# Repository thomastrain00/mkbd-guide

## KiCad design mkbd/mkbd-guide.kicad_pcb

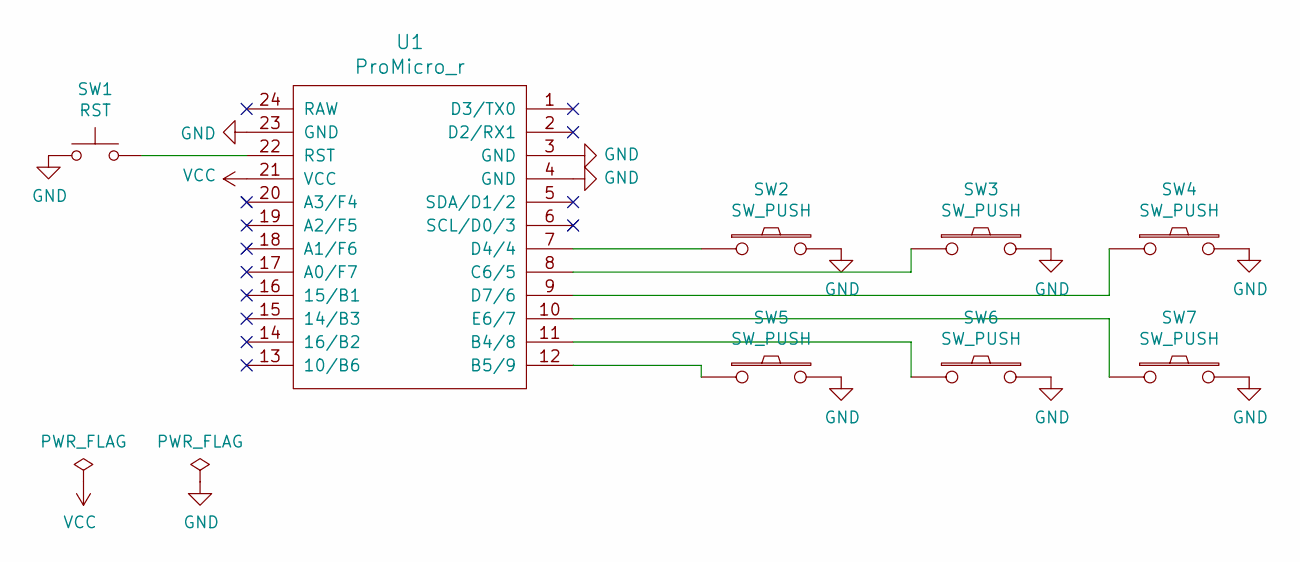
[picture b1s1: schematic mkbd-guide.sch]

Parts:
SW1: RST; ResetSW
SW2, SW3, SW4, SW5, SW6, SW7: SW_PUSH; CherryMX_1u
U1: ProMicro_r; ProMicro_v3

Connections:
GND: SW1.1, SW2.2, SW3.2, SW4.2, SW5.2, SW6.2, SW7.2, U1.3 (GND), U1.4 (GND), U1.23 (GND)
unnamed: SW1.2, U1.22 (RST)
unnamed: SW2.1, U1.7 (D4/4)
unnamed: SW3.1, U1.8 (C6/5)
unnamed: SW4.1, U1.9 (D7/6)
unnamed: SW5.1, U1.12 (B5/9)
unnamed: SW6.1, U1.11 (B4/8)
unnamed: SW7.1, U1.10 (E6/7)
VCC: U1.21 (VCC)

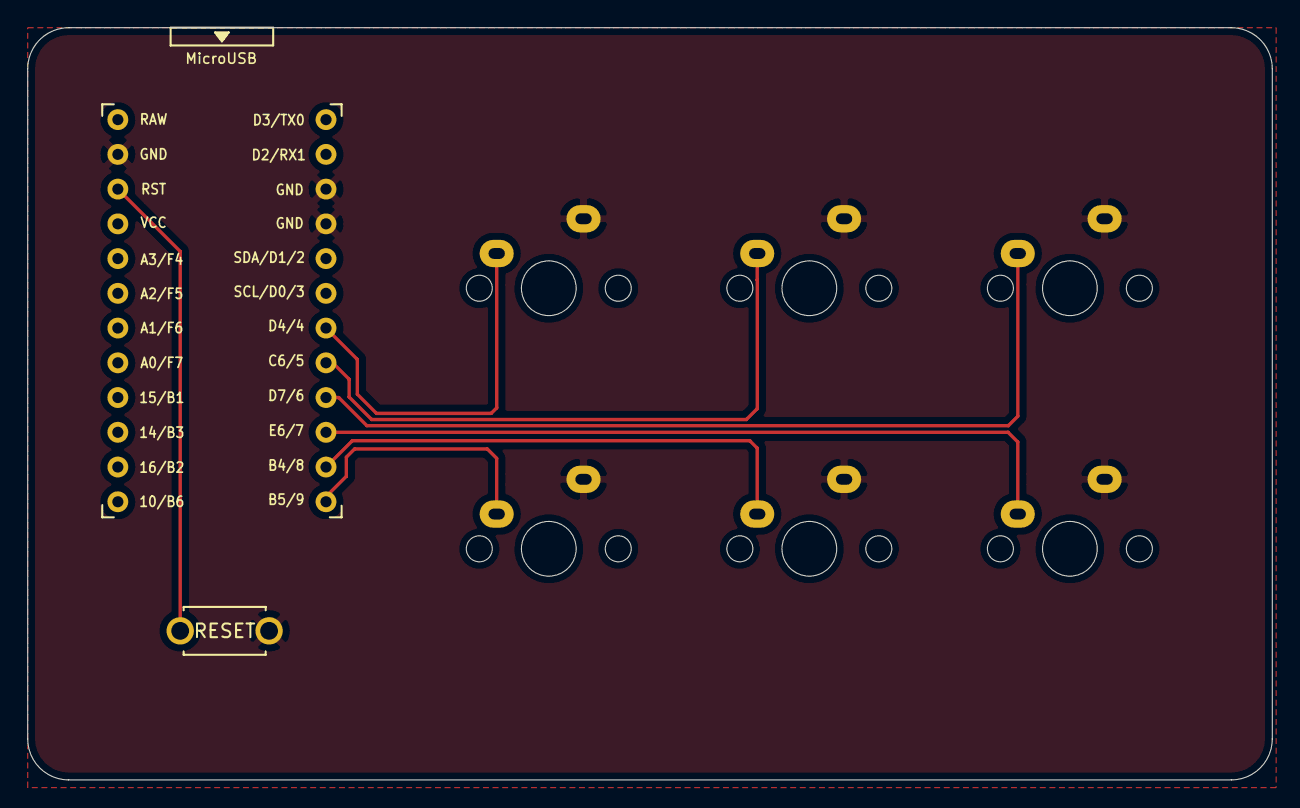
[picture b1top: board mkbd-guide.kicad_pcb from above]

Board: 2 copper layers, 91.0 x 55.0 mm, 8 parts (0 on the bottom side), 8 nets.

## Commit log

2021-05-15 Initialize project files
2021-05-16 Finished PCB
2021-05-17 Reorganize files
2021-05-17 Added silkscreen and gerbers
2021-05-19 Fixed gerbers
